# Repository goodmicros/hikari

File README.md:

# requirements

* WLED compatible
* battery powered with the possibility to bypass with USB power
* brightness comparable to a strip of ws2812b leds
* programmable without external hardware

# fixme

* LED footprint is confusing as the silkscreen EP marking is pointing to pin 1, not the cathode (pin 8)

# TODO

* micro-usb to type-c
* battery connector needs to be 2 through holes for AWG24 with the soldermask intact on the bottom side
* change the second button to a power switch?
* mounting holes
* gather datasheets to a common location

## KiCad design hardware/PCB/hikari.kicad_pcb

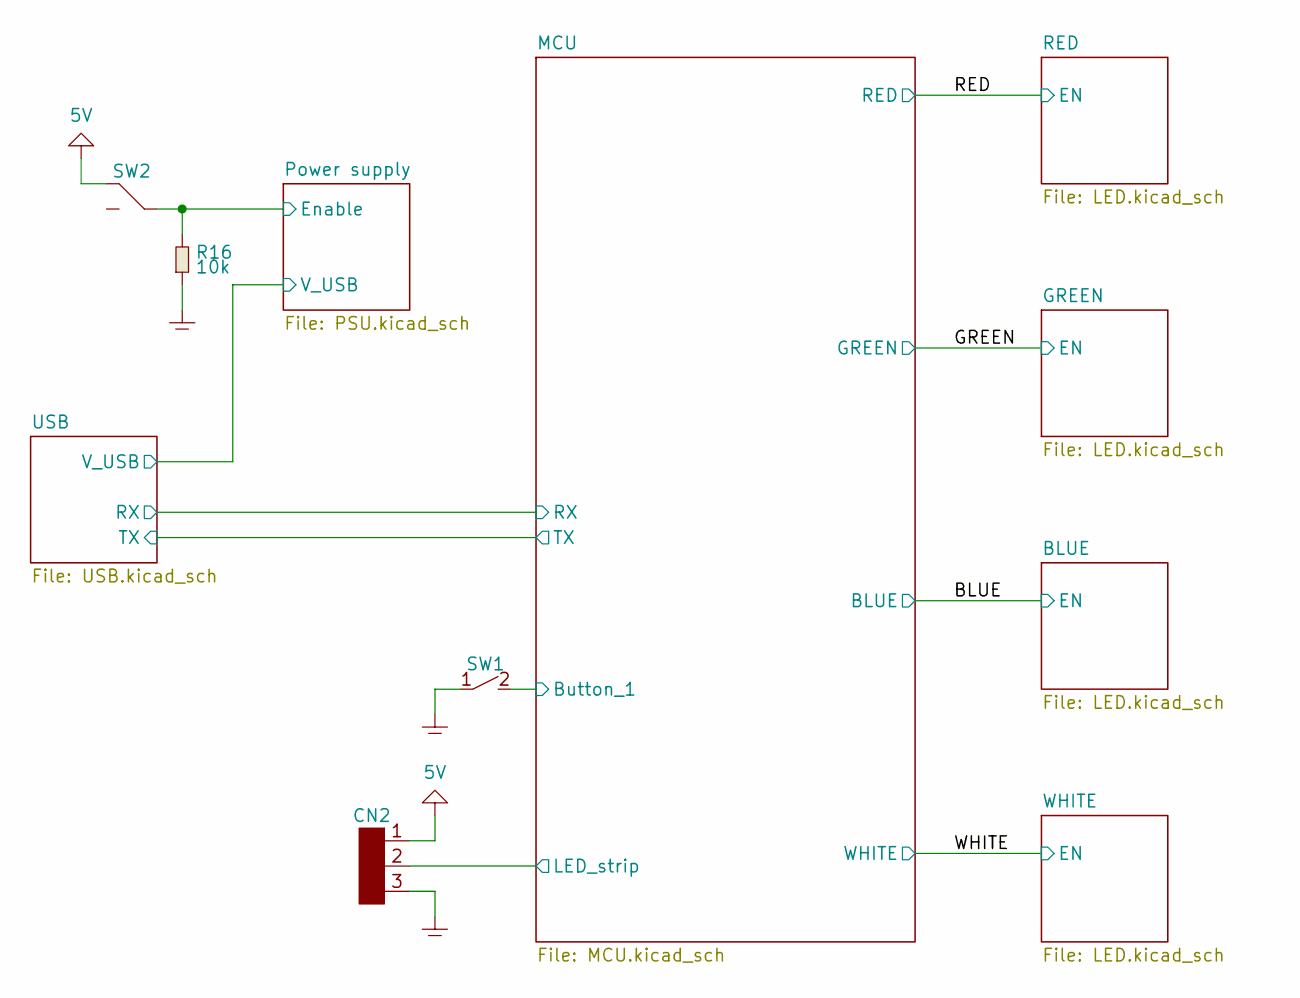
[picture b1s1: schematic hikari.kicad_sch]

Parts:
CN2: 1x3
R16: 10k; 0603; Digi-Key 13-RC0603JR-1010KLCT-ND
SW1: LS12W3-T; Digi-Key 1642-LS12W3-TCT-ND
SW2: JS102011SAQN; Digi-Key 401-1999-1-ND

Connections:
5V: CN2.1, SW2.1; also elsewhere on the board
/MCU/Button_1: SW1.2; also elsewhere on the board
/MCU/LED_strip: CN2.2; also elsewhere on the board
/Power supply/Enable: R16.2, SW2.2; also elsewhere on the board
GND: CN2.3, R16.1, SW1.0, SW1.1; also elsewhere on the board
unnamed: SW2.3, SW2.4

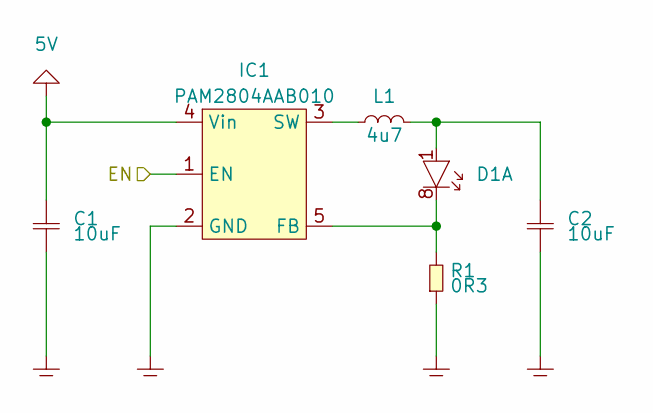
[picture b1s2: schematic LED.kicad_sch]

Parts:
C1, C2: 10uF; 0603; Digi-Key 1276-1119-1-ND
D1: QLSP06RGBXWAJ; 3030_8; MPN QLSP06RGBXWAJ; Digi-Key 3970-QLSP06RGBXWAJCT-ND
IC1: PAM2804AAB010; SOT-23-5; MPN PAM2804AAB010; Digi-Key PAM2804AAB010DICT-ND
L1: 4u7; CDRH2D11; Digi-Key 308-1590-1-ND
R1: 0R3; 0603; Digi-Key 273-KDV06FR300ETCT-ND

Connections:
5V: C1.1, IC1.4 (Vin); also elsewhere on the board
/RED: IC1.1 (EN); also elsewhere on the board
GND: C1.2, C2.2, IC1.2 (GND), R1.1; also elsewhere on the board
unnamed: C2.1, D1.1 (A), L1.2
unnamed: D1.8 (K), IC1.5 (FB), R1.2
unnamed 21: D1.2 (A); also elsewhere on the board
unnamed 22: D1.7 (K); also elsewhere on the board
unnamed 23: D1.3 (A); also elsewhere on the board
unnamed 24: D1.6 (K); also elsewhere on the board
unnamed 25: D1.4 (A); also elsewhere on the board
unnamed 26: D1.5 (K); also elsewhere on the board
unnamed: IC1.3 (SW), L1.1

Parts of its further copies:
C3, C4, C5, C6, C7, C8: 10uF; 0603; Digi-Key 1276-1119-1-ND
IC2, IC3, IC4: PAM2804AAB010; SOT-23-5; MPN PAM2804AAB010; Digi-Key PAM2804AAB010DICT-ND
L2, L3, L4: 4u7; CDRH2D11; Digi-Key 308-1590-1-ND
R2, R3, R4: 0R3; 0603; Digi-Key 273-KDV06FR300ETCT-ND

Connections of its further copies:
5V: C3.1, C5.1, C7.1, IC2.4 (Vin), IC3.4 (Vin), IC4.4 (Vin); also elsewhere on the board
/BLUE: IC3.1 (EN); also elsewhere on the board
/GREEN: IC2.1 (EN); also elsewhere on the board
/WHITE: IC4.1 (EN); also elsewhere on the board
GND: C3.2, C4.2, C5.2, C6.2, C7.2, C8.2, IC2.2 (GND), IC3.2 (GND), IC4.2 (GND), R2.1, R3.1, R4.1; also elsewhere on the board
unnamed 21: C4.1, L2.2; also elsewhere on the board
unnamed 22: IC2.5 (FB), R2.2; also elsewhere on the board
unnamed 23: C6.1, L3.2; also elsewhere on the board
unnamed 24: IC3.5 (FB), R3.2; also elsewhere on the board
unnamed 25: C8.1, L4.2; also elsewhere on the board
unnamed 26: IC4.5 (FB), R4.2; also elsewhere on the board
unnamed: IC2.3 (SW), L2.1
unnamed: IC3.3 (SW), L3.1
unnamed: IC4.3 (SW), L4.1

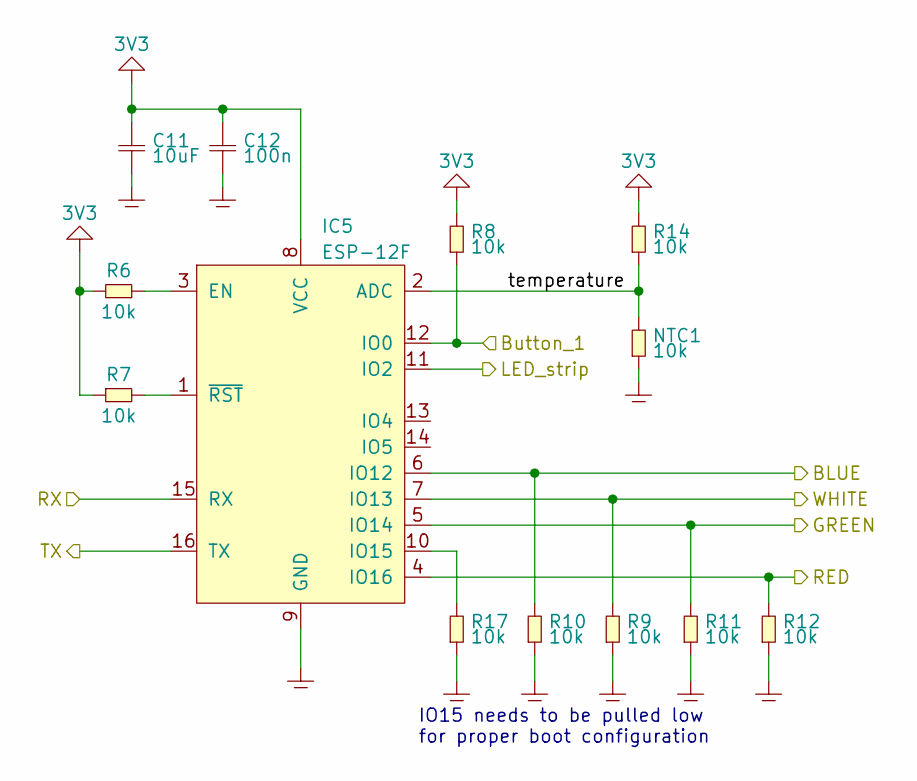
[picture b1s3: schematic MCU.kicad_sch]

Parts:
C11: 10uF; 0603; Digi-Key 1276-1119-1-ND
C12: 100n; 0603; Digi-Key 1276-1935-1-ND
IC5: ESP-12F
NTC1: 10k; 0603; Digi-Key 490-16279-1-ND
R6, R7, R8, R9, R10, R11, R12, R14, R17: 10k; 0603; Digi-Key 13-RC0603JR-1010KLCT-ND

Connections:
3V3: C11.1, C12.1, IC5.8 (VCC), R6.2, R7.1, R8.2, R14.2; also elsewhere on the board
/BLUE: IC5.6 (IO12), R10.2; also elsewhere on the board
/GREEN: IC5.5 (IO14), R11.2; also elsewhere on the board
/MCU/Button_1: IC5.12 (IO0), R8.1; also elsewhere on the board
/MCU/LED_strip: IC5.11 (IO2); also elsewhere on the board
/MCU/RX: IC5.15 (RX); also elsewhere on the board
/MCU/TX: IC5.16 (TX); also elsewhere on the board
/MCU/temperature: IC5.2 (ADC), NTC1.2, R14.1
/RED: IC5.4 (IO16), R12.2; also elsewhere on the board
/WHITE: IC5.7 (IO13), R9.2; also elsewhere on the board
GND: C11.2, C12.2, IC5.9 (GND), NTC1.1, R9.1, R10.1, R11.1, R12.1, R17.1; also elsewhere on the board
unnamed: IC5.3 (EN), R6.1
unnamed: IC5.10 (IO15), R17.2
unnamed: IC5.1 (~RST), R7.2

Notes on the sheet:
IO15 needs to be pulled low for proper boot configuration

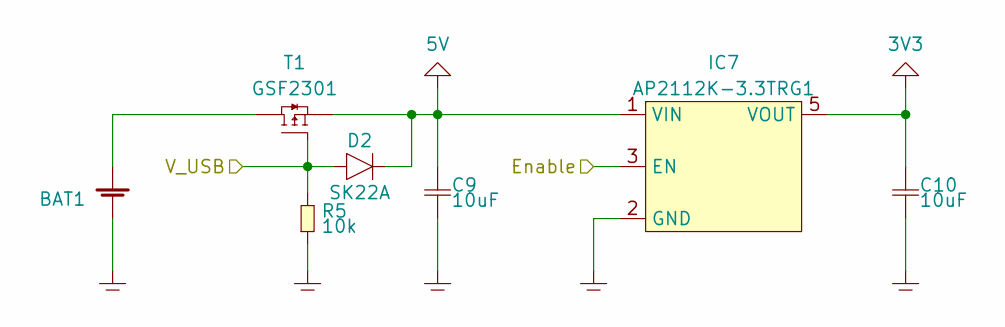
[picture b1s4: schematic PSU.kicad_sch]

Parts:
BAT1: Battery; Battery_solder-points
C9, C10: 10uF; 0603; Digi-Key 1276-1119-1-ND
D2: SK22A; DO-214AC; Digi-Key 4786-SK22ACT-ND
IC7: AP2112K-3.3TRG1; SOT-23-5; MPN AP2112K-3.3TRG1; Digi-Key AP2112K-3.3TRG1DICT-ND
R5: 10k; 0603; Digi-Key 13-RC0603JR-1010KLCT-ND
T1: GSF2301; SOT-23; Digi-Key 4786-GSF2301CT-ND

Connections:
3V3: C10.1, IC7.5 (VOUT); also elsewhere on the board
5V: C9.1, D2.2 (K), IC7.1 (VIN), T1.2 (S); also elsewhere on the board
/Power supply/Enable: IC7.3 (EN); also elsewhere on the board
/Power supply/V_USB: D2.1 (A), R5.2, T1.1 (G); also elsewhere on the board
GND: BAT1.2 (-), C9.2, C10.2, IC7.2 (GND), R5.1; also elsewhere on the board
unnamed: BAT1.1 (+), T1.3 (D)

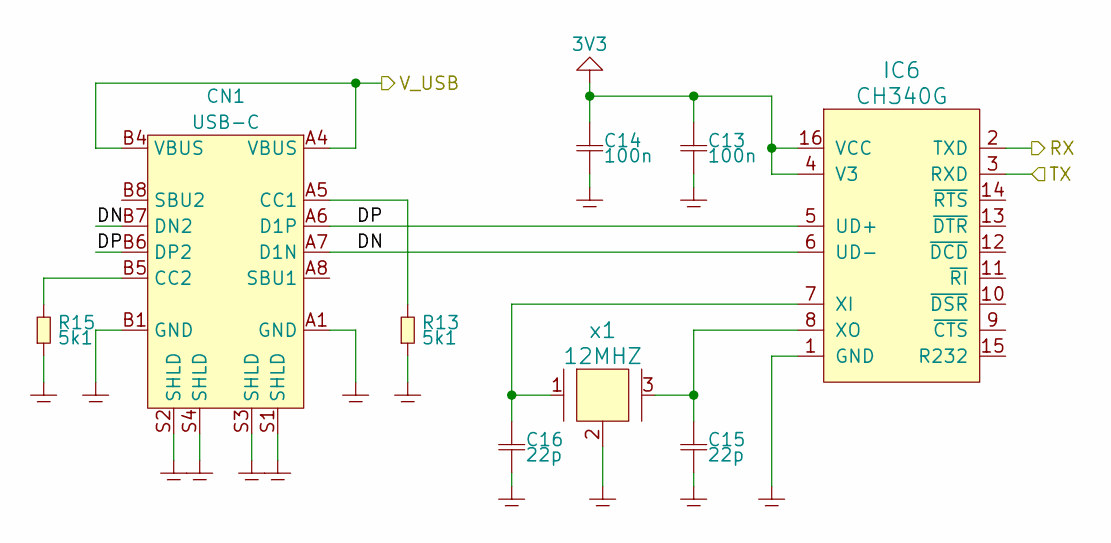
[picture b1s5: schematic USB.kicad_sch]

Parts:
C13, C14: 100n; 0603; Digi-Key 1276-1935-1-ND
C15, C16: 22p; 0603; Digi-Key 1292-1503-1-ND
CN1: USB-C; USB4105-GF-A; MPN USB4105-GF-A; Digi-Key 2073-USB4105-GF-ACT-ND
IC6: CH340G; SOP-16
R13, R15: 5k1; 0603; Digi-Key 13-RC0603FR-135K1LCT-ND
x1: 12MHZ; 3.2x2.5CXO; Digi-Key 2151-RH100-12.000-18-2020-EXT-TRCT-ND

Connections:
3V3: C13.1, C14.1, IC6.4 (V3), IC6.16 (VCC); also elsewhere on the board
/MCU/RX: IC6.2 (TXD); also elsewhere on the board
/MCU/TX: IC6.3 (RXD); also elsewhere on the board
/Power supply/V_USB: CN1.A4 (VBUS), CN1.B4 (VBUS); also elsewhere on the board
/USB/DN: CN1.A7 (D1N), CN1.B7 (DN2), IC6.6 (UD-)
/USB/DP: CN1.A6 (D1P), CN1.B6 (DP2), IC6.5 (UD+)
GND: C13.2, C14.2, C15.2, C16.2, CN1.A1 (GND), CN1.B1 (GND), CN1.S1 (SHLD), CN1.S2 (SHLD), CN1.S3 (SHLD), CN1.S4 (SHLD), IC6.1 (GND), R13.1, R15.1, x1.2, x1.4; also elsewhere on the board
unnamed: CN1.A5 (CC1), R13.2
unnamed: CN1.B5 (CC2), R15.2
unnamed: C16.1, IC6.7 (XI), x1.1
unnamed: C15.1, IC6.8 (XO), x1.3

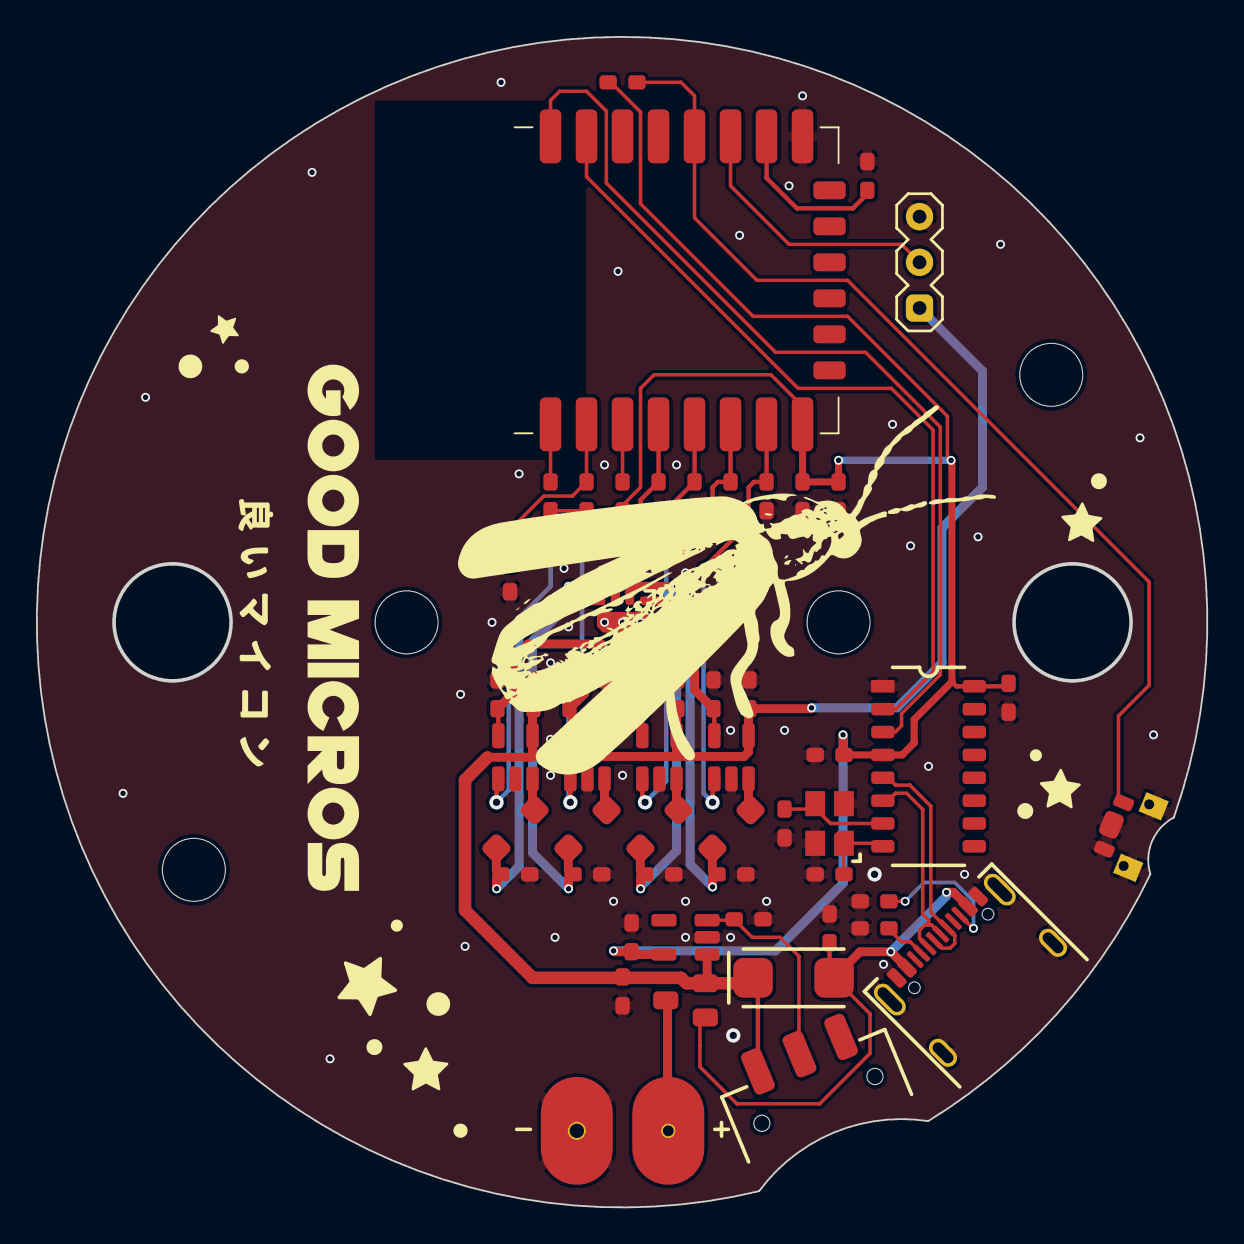
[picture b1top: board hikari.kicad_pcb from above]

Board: 2 copper layers, 65.0 x 65.0 mm, 54 parts (0 on the bottom side), 36 nets.

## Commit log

2023-04-27 created schematic hierarchy
2023-05-10 added usb serial and mcu
2023-05-17 cleaned up layout, added 3V3 regulator, changed NTC to connect to gnd instead of 3V3, added README
2023-05-19 added esp12 footprint
2023-05-23 fixed power symbols from showing up in BOM
2023-05-23 started layout, updated readme, annotated power symbols...
2023-05-29 worked layout, fixed 3V3 being GND net
2023-05-30 added type-c connector
2023-06-05 did most of todo items
2023-06-06 rough layout done
2023-06-06 all signals routed
2023-06-06 added graphics on top silk
2023-06-07 added gaps on pcb under switches
2023-06-07 added clearance from copper pour to pcb edge, increased soldermask openings, DRC ok
2023-06-07 added Digi-Key part numbers to BOM
2023-06-08 reviewn completed, fixes required
2023-06-12 fixed errors, ready for order
2023-06-13 added step, preview. fixed hole diameter being documented 6 mm
2023-06-27 added pcb hoder for stencil work
2023-06-30 Added hikari case stl files
2023-06-30 Added link to Onshape model
2023-07-18 Tiny support added
2023-08-01 updated documentation
2023-08-02 updated photo
2023-08-07 Update readme.md
    added button information and installing stuff
2023-08-07 Restructured / refined readme.md
2023-08-07 Added links to native apps
2023-08-15 moved pcb and scad files under hardware
2023-08-15 added default config and presets
2024-12-12 fixed the pcb being powered via ch340g
